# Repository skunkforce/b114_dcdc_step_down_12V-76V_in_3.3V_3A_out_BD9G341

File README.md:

# edgy_board number b114
This design is part of the [edgy board project](https://github.com/skunkforce/edgy_boards). It provides a 3A 3.3V switching step-down regulator with a wide input voltage range. 

# getting started
This repository uses submodules. After cloning use the command 

```$ git submodule update --init --recursive```

to pull the submodules before opening the project with kicad. 

# Tests
Tests can be found in [TESTS.md](TESTS.md)

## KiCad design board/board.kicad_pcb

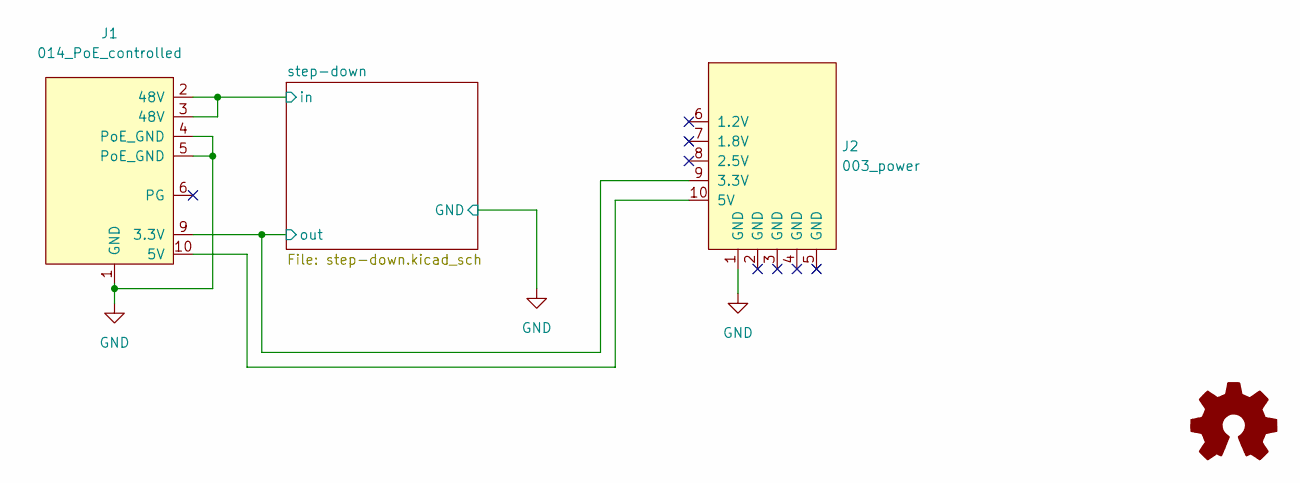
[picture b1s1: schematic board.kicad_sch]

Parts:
J1: 014_PoE_controlled; on_edge_2x05_device
J2: 003_power; on_edge_2x05_host
LOGO1: Logo_Open_Hardware_Small; OSHW-Symbol_6.7x6mm_SilkScreen

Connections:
/step-down/in: J1.2 (48V), J1.3 (48V); also elsewhere on the board
/step-down/out: J1.9 (3.3V), J2.9 (3.3V); also elsewhere on the board
GND: J1.1 (GND), J1.4 (PoE_GND), J1.5 (PoE_GND), J2.1 (GND); also elsewhere on the board
unnamed: J1.10 (5V), J2.10 (5V)

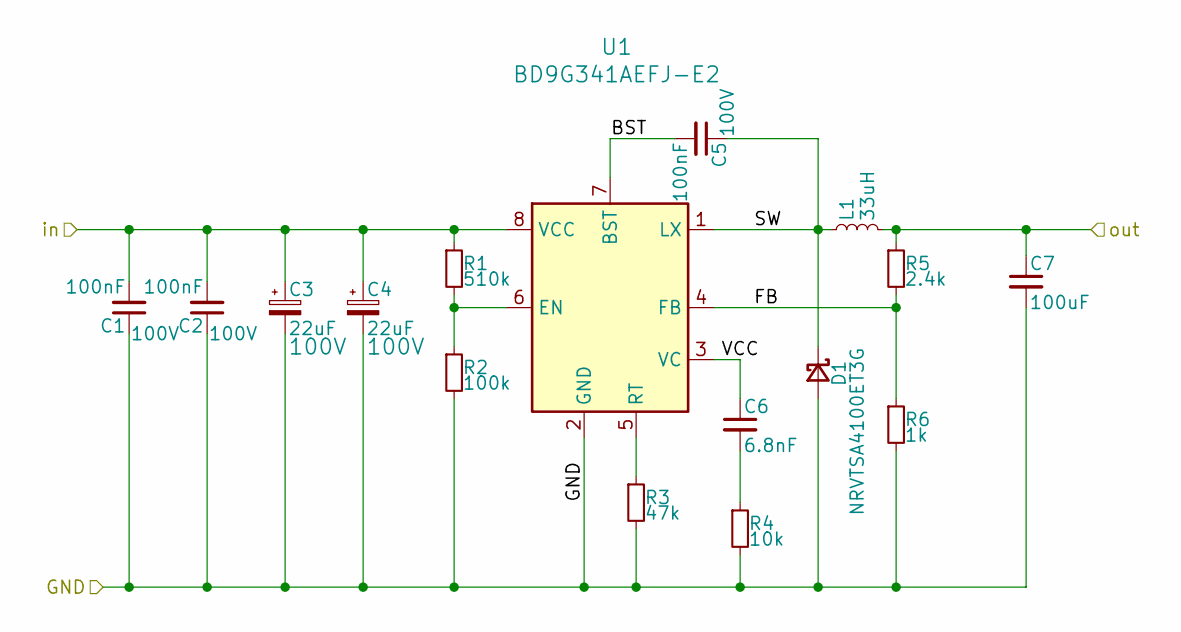
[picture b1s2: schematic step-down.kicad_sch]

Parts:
C1, C2, C5: 100nF; C_0603_1608Metric; Voltage 100V; Digi-Key_PN 1276-6807-1-ND
C3, C4: 22uF; CP_Elec_8x10; Voltage 100V; MPN 865080853006; lcsc C29144
C6: 6.8nF; C_0603_1608Metric; Voltage 6.3V; Digi-Key_PN 1276-1185-1-ND‎
C7: 100uF; C_1210_3225Metric; Voltage 6.3V; MPN 885012109004; Digi-Key_PN 732-7375-1-ND
D1: NRVTSA4100ET3G; D_SMA; MPN NRVTSA4100ET3G; Digi-Key_PN NRVTSA4100ET3GOSCT-ND
L1: 33uH; L_Bourns_SRR1210A; MPN 7447714330; lcsc C2983067
R1: 510k; R_0603_1608Metric; MPN RMCF0603JT510K‎; Digi-Key_PN ‎RMCF0603JT510KCT-ND‎
R2: 100k; R_0603_1608Metric; lcsc C25803
R3: 47k; R_0603_1608Metric; lcsc C25819
R4: 10k; R_0603_1608Metric; lcsc C25804
R5: 2.4k; R_0603_1608Metric; lcsc C22940
R6: 1k; R_0603_1608Metric; lcsc C21190
U1: BD9G341AEFJ-E2; SOIC-8-1EP_3.9x4.9mm_P1.27mm_EP2.29x3mm_ThermalVias; lcsc C2981600

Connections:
/step-down/BST: C5.2, U1.7 (BST)
/step-down/FB: R5.2, R6.1, U1.4 (FB)
/step-down/SW: C5.1, D1.1 (K), L1.1, U1.1 (LX)
/step-down/VCC: C6.1, U1.3 (VC)
/step-down/in: C1.2, C2.2, C3.1, C4.1, R1.1, U1.8 (VCC); also elsewhere on the board
/step-down/out: C7.1, L1.2, R5.1; also elsewhere on the board
GND: C1.1, C2.1, C3.2, C4.2, C7.2, D1.2 (A), R2.2, R3.2, R4.2, R6.2, U1.2 (GND), U1.9 (GND); also elsewhere on the board
unnamed: C6.2, R4.1
unnamed: R1.2, R2.1, U1.6 (EN)
unnamed: R3.1, U1.5 (RT)

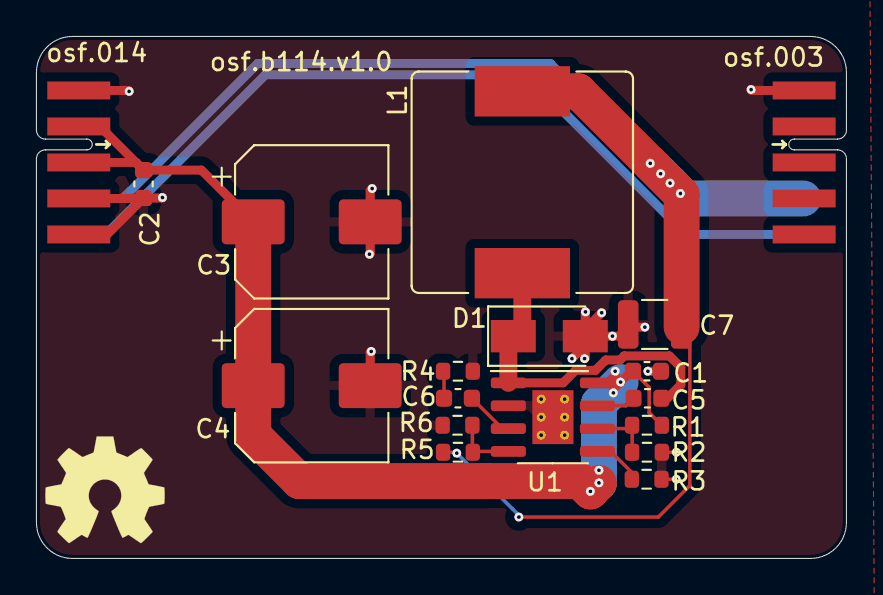
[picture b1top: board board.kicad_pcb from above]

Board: 2 copper layers, 45.0 x 29.0 mm, 19 parts (0 on the bottom side), 11 nets.

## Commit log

2023-03-22 initial
2024-01-31 added lcsc part numbers
